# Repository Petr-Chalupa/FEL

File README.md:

<!-- omit from toc -->
# FEL
This repository contains selected coursework completed during my studies in
OI at CTU FEL. \
_If you found this repo. because you need help with some homework, do not copy, just get an inspiration :)_

<!-- omit from toc -->
## Theoretical Foundations
- LAG - Linear Algebra
- DMA - Discrete Mathematics
- LGR - Logic and Graph Theory
- MA1, MA2 - Mathematical Analysis I & II
- PST - Probability and Statistics
- NUM - Numerical Methods
- OPT - Optimization
- PKS - Computer and Communication Networks

<!-- omit from toc -->
## Programming & Engineering Courses
- [PRP - C](#prp---c)
- [RPH - Python](#rph---python)
- [PJV - Java](#pjv---java)
- [APO - Assembly \& C](#apo---assembly--c)
- [FUP - Racket \& Haskell](#fup---racket--haskell)
- [PSIA - C](#psia---c)
- [ALG - C](#alg---c)
- [OSY - Shell \& C](#osy---shell--c)
- [KEO - Hardware](#keo---hardware)
- [PDV - C++ \& Java](#pdv---c--java)
- [ZUI - Python](#zui---python)
- [DBS - SQL \& Java](#dbs---sql--java)

### PRP - C
- Command Line Tools ~ utilities demonstrating C programming concepts:
  - Array and string manipulation (hw01, hw02)
  - File operations and parsing (hw03)
  - Data structures implementation (hw04, hw05)
  - Memory management (hw06)
  - Custom grep implementation (hw07)
- Graph Algorithms ~ implementations of fundamental graph operations and algorithms:
  - Queue implemetation (hw08)
  - File I/O for both text and binary formats (hw09)
  - Memory management with dynamic allocation (hw09)
  - Implementations of various graph algorithms (hw10)
  - _Note: hw10 framework was provided, my contribution was integration of specific functions (pq_update, dijkstra_set_graph, dijkstra_get_solution, graph.c)_

### RPH - Python
- Spam Filter ~ a modular email classification system with various spam detection methods:
  - Multiple filter types (Naive, Paranoid, Random and advanced heuristic Filter)
  - Analyzes email headers, domains, subject keywords, text patterns and links
  - Uses confusion matrix for quality assessment
  - Training and testing on email corpus data
- Reversi ~ a player implementation for the Reversi board game:
  - Heuristic-based move selection
  - Position rating matrix
  - Valid move detection with weighted decision-making
  - Complete game rules implementation

### PJV - Java
- Core Java Concepts - Standalone assignments demonstrating Java fundamentals:
  - Calculator (console-based arithmetic operations)
  - CircularArrayQueue (queue implementation with fixed capacity)
  - SequenceStats (statistical calculations on number sequences)
  - BruteForceAttacker (recursive password cracking with a character set)
  - Tree & Node (binary tree with recursive traversal and string representation)
- [2D Game Engine](https://github.com/Petr-Chalupa/JTileEngine) - Semester project implementing a custom 2D game engine in JavaFX

### APO - Assembly & C
- Assembly Assignments (RISC-V):
  - Array manipulation and sorting algorithms in assembly (hw02.S, lab01.S, lab02.S)
  - Serial port I/O echo implementation (lab03.S)
  - Fibonacci sequence generation on a pipelined CPU (hw03.S)
  - 32-bit word to hexadecimal digits conversion and serial port output (hw04.S)
  - _Note: All assembly code is tested in [QtRVSim](https://github.com/cvut/qtrvsim) - a RISC-V simulator_
- C Assignments:
  - Image convolution using a mask (hw01.c)
  - UART calculator for adding unsigned numbers, built without static libraries (hw05.c)
    - _Note: hw05_crt0.S was provided as a minimal replacement for C runtime_
  - Simple LCD program (lab04.c)
- Pong Game (C):
  - Implementation of the classic Pong game for the MZ-APO educational board
  - Features:
    - Real-time graphics rendering on the LCD
    - Paddle and ball movement with collision detection
    - Score tracking and high scores
    - Modular code structure for hardware abstraction
  - _Note: Only the following files are my original work:_
    - _`pong.c`, `utils.c`, `IO_utils.c`, `logo.c` and their respective header files in `include/`_
    - _Other files (e.g., hardware abstraction, font data) were provided as part of the assignment framework._

### FUP - Racket & Haskell
- Racket Assignments:
  - Image Processing ~ ASCII art generation from images (hw01):
    - Image to grayscale matrix conversion
    - Matrix scaling and transformation
    - ASCII character mapping based on pixel intensity
    - Support for custom character sets and block sizes
  - SVG Generator ~ declarative SVG generation (hw02):
    - Dynamic SVG element creation
    - Support for basic shapes (circle, rect, line)
    - Expression evaluation with environments
    - Conditional rendering capabilities
  - Exam assigment - Manhattan distance (exam01.rkt):
    - Assigns symbols to grid cells based on proximity to given points
    - Handles ties and exact matches with special symbols
- Haskell Assignments:
  - λ-Calculus Evaluator (Hw03)
    - Lambda calculus interpreter with normal order reduction
    - Alpha conversion, beta reduction and capture-avoiding substitution
    - Leftmost redex finding for proper evaluation order
    - Expression representation for variables, applications, and abstractions
  - Parser of λ-programs (Hw04)
    - Parser implementation for λ-calculus expressions
    - Support for variable definitions and substitutions
    - _Note: Parser monad implementation was provided_
  - Exam assigment - Minimum spanning tree (Exam02.hs):
    - Minimum spanning tree computation using Jarník's algorithm
    - Custom graph and edge data types
    - Handles undirected graphs by edge reversal

### PSIA - C
- Network Programming ~ UDP File Transfer:
    - CRC32 packet verification
    - MD5 file integrity check
    - Selective repeat and stop-and-wait for flow control
    - Automatic retry on packet loss
    - Configurable window size and packet size
  - Client-Server Architecture
    - Configurable ports and IP addresses
  - File Operations
    - Binary file transfer support
    - Integrity verification
  - _Note: [md5](https://github.com/Zunawe/md5-c) is a publicly available library_

### ALG - C
- Duplicate Number Finder (hw00.c):
    - Training exercise
- Park Designer (hw01.c):
    - Optimizes park layout with specific constraints:
      - Central area must contain minimum number of rocks
      - Maximizes number of forest tiles in total area
    - Uses prefix sum arrays for efficient area calculations
- Agent Placement (hw02.c):
    - Optimizes agent placement in a graph:
      - Type A scores based on occupied neighbors
      - Type B scores based on unoccupied neighbors
    - Uses backtracking with pruning optimizations
- Tree Path Finder (hw03.c):
    - Finds longest valid path in a tri-colored tree:
      - Path cannot contain 3 consecutive same-colored nodes
    - Uses recursive DFS with path validation
    - Queue-based tree construction from level-order input
- Mouse vs Cat Path (hw04.c):
    - Finds shortest "safe" path for a mouse while avoiding the cat:
      - Graph nodes can be "noisy"; visiting noisy nodes alerts the cat
      - Mouse must avoid positions reachable by the cat within constrained jumps
    - Uses multi-state per node storage and BFS with pruning to return (distance, noisy_used) for optimal path
- Binary search tree with lazy deletion (hw05.c):
    - Implements a BST that supports `ins K` and `del K` commands.
    - Uses lazy deletion and periodically compacts the tree when the sum of deleted-node heights exceeds the sum of active-node heights.
    - Compaction preserves pre-order of active nodes
- Turing machine simulator (hw06.c):
  - Decodes a compact machine encoding into transitions and simulates the machine
  - Checks whether the machine is deterministic and explores branching configurations using BFS
- Irrigatio (hw07.c):
  - Selects high-value horizontal/vertical segments using prefix-sums
  - Sorts segments by weight and combines them via DP for optimal total value
- Totem Buyer (hw08.c):
  - Maximizes profit from buying totems between villages and selling them
  - Villages merge when their separating totem is purchased
  - Purchase cost depends on warrior count difference between villages
  - Similar structure to matrix chain multiplication problem
- Triples (exam.c):
  - Finds non-overlapping 3-cell segments (horizontal and vertical) in a colored matrix
  - Scores each segment: 3 points for all same color, 1 point for 2 same colors, 0 points otherwise
  - Uses backtracking to maximize total score by selecting optimal segment combinations
  - Includes pruning optimization with greedy upper bound calculation for performance

### OSY - Shell & C
- Shell Scripting:
  - File System Path Processor (hw01.sh):
    - Processes paths from stdin (prefixed with "PATH ")
    - Optional .tgz archive creation (-z flag)
  - Text Processing Utilities (hw02.sh):
    - PDF file listing with case-insensitive sorting
    - Number-prefixed line filtering
    - Sentence extraction and formatting
    - C #include directive prefix manipulation
- Unix Programming:
  - Process forking and piping (hw03):
    - Parent-child process communication via pipes
    - Random number generator with signal handling
    - Integration with provided GCD calculator
    - _Note: `nsd_src` (GCD calculator) was provided as part of the assignment_
  - Producer-Consumer Threading (hw04):
    - Multithreaded word processing with shared list
    - Mutex-protected stdout and list operations
    - Conditional variables for synchronization
  - Factory Simulation (hw05):
    - Command-driven factory simulator reading commands from stdin
    - Worker threads process product steps at named places
    - Synchronization with mutexes and condition variables
    - Dynamic worker management and resource accounting
  - Hexadecimal Converter (hw06):
    - Reads unsigned integers from stdin and prints them as hexadecimal
    - Implementation using direct syscalls
    - Built with no libc
- Nova Microkernel Assignments:
  - nbrk system call (ec_syscall.cc):
    - Handles dynamic memory with page table operations and allocation/deallocation
  - User-space memory allocator (mem_alloc.c):
    - Custom heap management for user programs
    - Integrates with kernel page management
  - Thread management system calls (ec_syscall.cc):
    - thread_create: Creates new threads with user-provided stack
    - thread_yield: Switches execution context to the next thread in buffer
    - Circular queue scheduler
  - _Note: Nova kernel framework, build system, and infrastructure were provided; my contributions are `ec_syscall.cc` and `mem_alloc.c`._
    - _The kernel framework provides: CPU/MMU abstraction (`cpu.h`, `ptab.h`), physical memory manager (`kalloc.h`), execution context infrastructure (`ec.h`)..._

### KEO - Hardware
- Complete PCB project design and realization
- Documentation: [`Prezentace.pdf`](KEO/Prezentace.pdf), [`Protokol.pdf`](KEO/Protokol.pdf), [`Schema.pdf`](KEO/Schema.pdf), [`DPS.pdf`](KEO/DPS.pdf)
- Design files: [`Zdroj.kicad_sch`](KEO/Zdroj/Zdroj.kicad_sch), [`Zdroj.kicad_pcb`](KEO/Zdroj/Zdroj.kicad_pcb), [`Zdroj.kicad_pro`](KEO/Zdroj/Zdroj.kicad_pro)

### PDV - C++ & Java
- Parallel (C++):
  - Producer-Consumer Threading (hw01):
    - Generic thread pool template with parametrized job and worker types
    - Producer-consumer coordination without busy-waiting
  - Vector Sum (hw02):
    - Parallel array summation using various OpenMP scheduling strategies
    - Comparison of `static` vs. `dynamic` scheduling performance for uneven workloads
    - Analysis of load balancing trade-offs
  - Lock-Free BST (hw03):
    - Thread-safe binary search tree using atomic operations and lock-free synchronization
    - Lock-free insertion and deletion with compare-and-swap operations
  - Parallel Database Query (hw04):
    - Evaluation of universal and existential predicates
    - Early termination using #pragma omp cancel for
  - Parallel Radix Sort (hw05):
    - Recursive MSD radix sort implementation for strings
    - Parallelized using recursive sub-sorting of buckets
- Distributed (Java):
  - BFS and IDDFS (hw06):
    - Parallel implementations of breadth-first search and iterative deepening depth-first search
    - _Note: Framework files were provided as part of the assignment_
  - SWIM Protocol (hw07):
    - Implementation of the SWIM failure detection protocol with custom active strategy and ping message handling
    - _Note: Framework files were provided as part of the assignment_
  - Ricart-Agrawala Mutual Exclusion (hw08):
    - Implementation of the Ricart-Agrawala algorithm for distributed mutual exclusion with logical clocks and message passing for critical sections coordination
    - _Note: Framework files were provided as part of the assignment_
  - RAFT Consensus (hw09):
    - Implementation of the RAFT distributed consensus protocol for replicated state machines
    - Leader election, log replication, and follower heartbeats with safety under message loss
    - Message classes for vote requests/responses and append entries for cluster coordination
    - _Note: Framework files were provided as part of the assignment_

### ZUI - Python
- Blocks World Solver (hw01):
  - A* search algorithm with custom heuristic for solving the blocks world puzzle
  - Heuristic based on correct prefix matching of goal stacks
  - Finds optimal sequence of block moves to reach goal configuration
  - _Note: blockworld.py environment was provided as part of the assignment_
- Tabular Q-Learning (hw02):
  - Reinforcement learning agent using tabular Q-learning to solve the blocks world puzzle
  - Custom implementation for training and evaluation
  - _Note: blockworld.py environment was provided as part of the assignment_
- OX Game Solver (hw03):
  - Implements Tic-Tac-Toe/OX game logic with self-play and move evaluation
  - Uses Monte Carlo Tree Search guided by a neural network model for position assessment
  - _Note: ox.py environment was provided as part of the assignment_

### DBS - SQL & Java
- Database Systems ~ SQL & Java assignments demonstrating relational modeling, ER design, and query construction
- Practical SQL problem solving and database design
  - _Note: `CP5.java` is the main important class in this section of assignment_

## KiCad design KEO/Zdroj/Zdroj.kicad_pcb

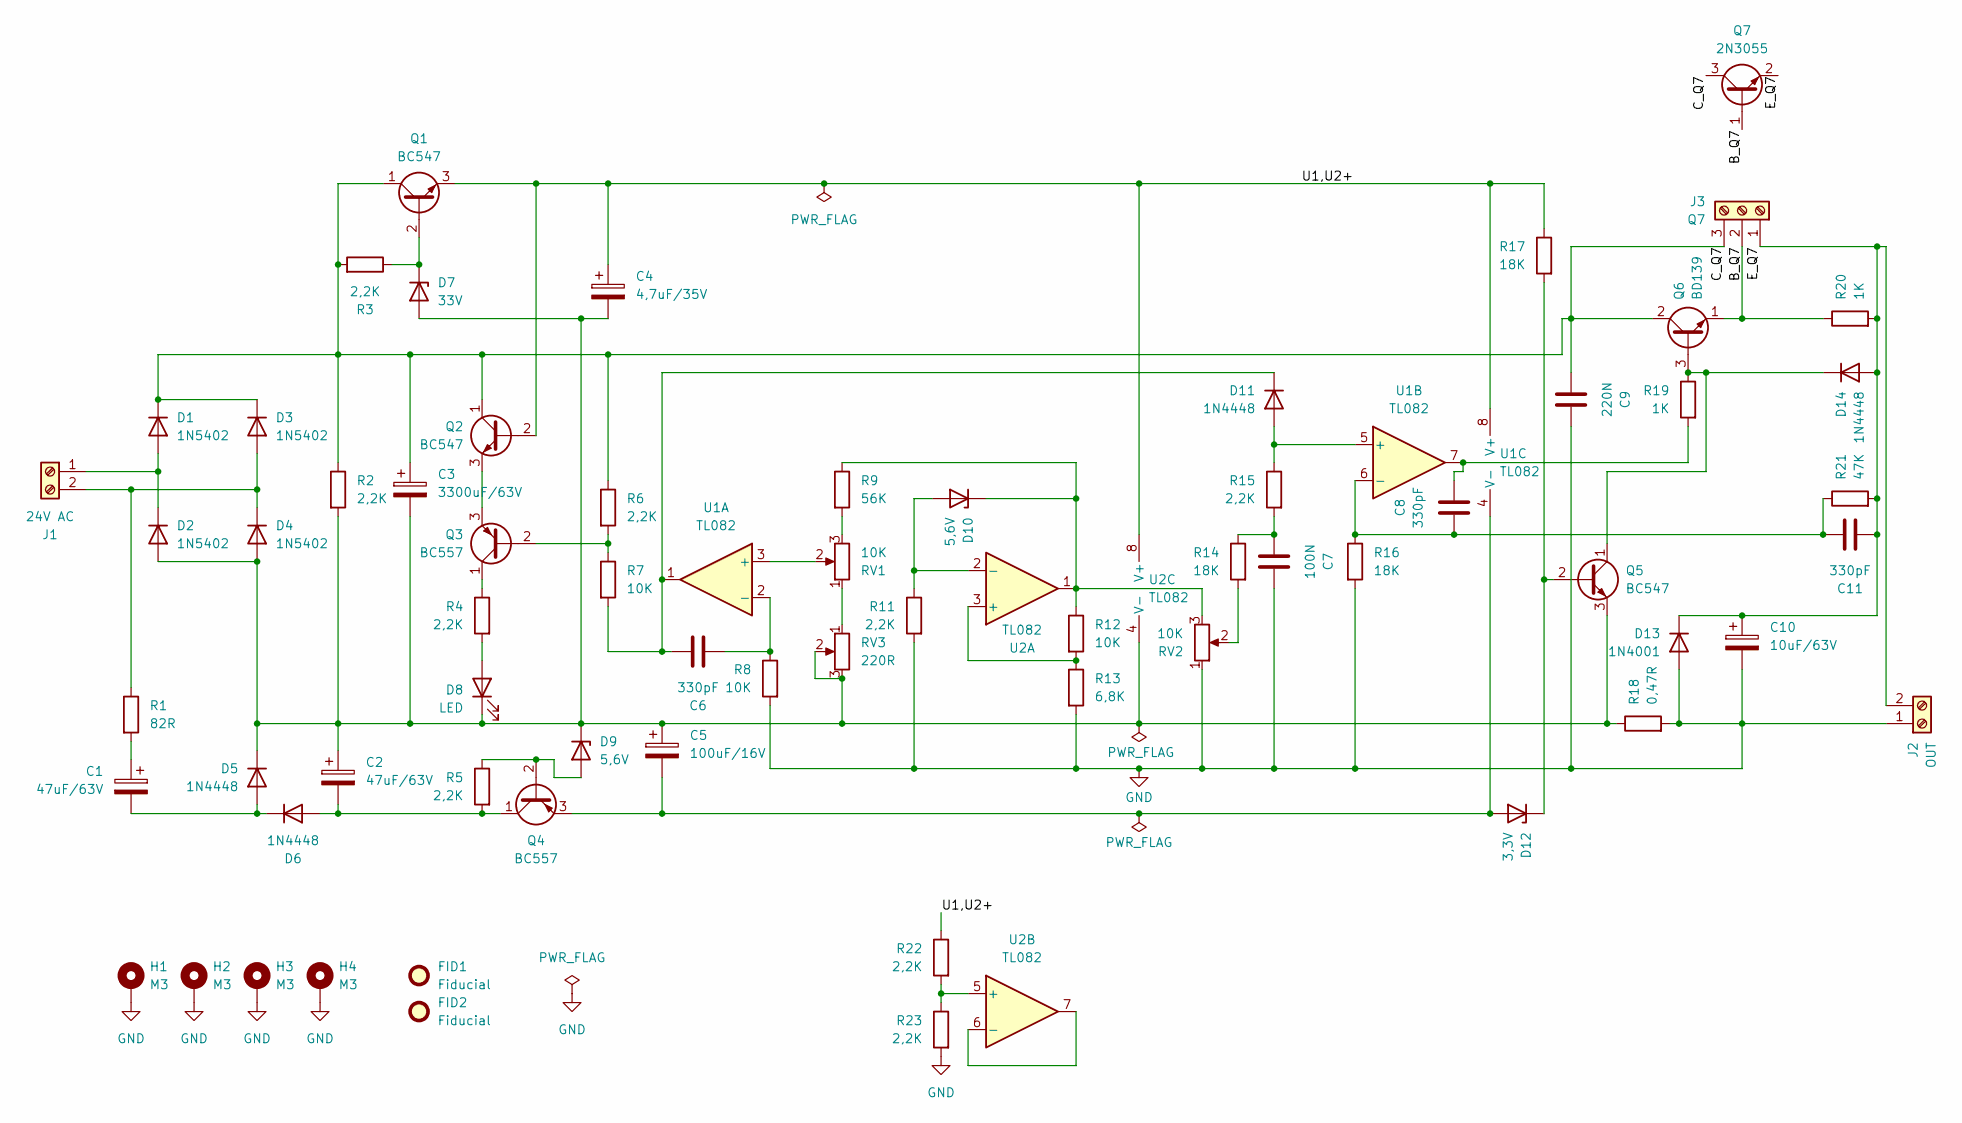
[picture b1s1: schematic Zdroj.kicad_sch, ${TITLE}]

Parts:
C1, C2: 47uF/63V; CP_Radial_D10.0mm_P5.00mm
C3: 3300uF/63V; CP_Radial_D22.0mm_P10.00mm_SnapIn
C4: 4,7uF/35V; CP_Radial_D5.0mm_P2.00mm
C5: 100uF/16V; CP_Radial_D6.3mm_P2.50mm
C6, C8, C11: 330pF; C_Disc_D5.0mm_W2.5mm_P5.00mm
C7: 100N; C_Rect_L7.0mm_W2.5mm_P5.00mm
C9: 220N; C_Rect_L7.0mm_W2.5mm_P5.00mm
C10: 10uF/63V; CP_Radial_D6.3mm_P2.50mm
D1, D2, D3, D4: 1N5402; D_DO-201AD_P15.24mm_Horizontal
D5, D6, D11, D14: 1N4448; D_DO-35_SOD27_P7.62mm_Horizontal
D7: 33V; D_DO-35_SOD27_P7.62mm_Horizontal
D8: LED; LED_D5.0mm
D9, D10: 5,6V; D_DO-35_SOD27_P7.62mm_Horizontal
D12: 3,3V; D_DO-35_SOD27_P7.62mm_Horizontal
D13: 1N4001; D_DO-41_SOD81_P10.16mm_Horizontal
FID1, FID2: Fiducial; Fiducial_0.5mm_Mask1mm
H1, H2, H3, H4: M3; MountingHole_3.2mm_M3_DIN965_Pad
J1: 24V AC; TerminalBlock_Phoenix_MKDS-3-2-5.08_1x02_P5.08mm_Horizontal
J2: OUT; TerminalBlock_Phoenix_MKDS-3-2-5.08_1x02_P5.08mm_Horizontal
J3: Q7; TerminalBlock_Phoenix_MKDS-1,5-3-5.08_1x03_P5.08mm_Horizont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
Q1, Q2, Q5: BC547; TO-92_Inline
Q3, Q4: BC557; TO-92_Inline
Q6: BD139; TO-126-3_Vertical
Q7: 2N3055; TO-3
R1: 82R; R_Axial_DIN0207_L6.3mm_D2.5mm_P7.62mm_Horizontal
R2: 2,2K; R_Axial_DIN0414_L11.9mm_D4.5mm_P15.24mm_Horizontal
R3, R4, R5, R6, R11, R15, R22, R23: 2,2K; R_Axial_DIN0207_L6.3mm_D2.5mm_P7.62mm_Horizontal
R7, R8, R12: 10K; R_Axial_DIN0207_L6.3mm_D2.5mm_P7.62mm_Horizontal
R9: 56K; R_Axial_DIN0207_L6.3mm_D2.5mm_P7.62mm_Horizontal
R13: 6,8K; R_Axial_DIN0207_L6.3mm_D2.5mm_P7.62mm_Horizontal
R14, R16, R17: 18K; R_Axial_DIN0207_L6.3mm_D2.5mm_P7.62mm_Horizontal
R18: 0,47R; R_Axial_Power_L25.0mm_W6.4mm_P30.48mm
R19, R20: 1K; R_Axial_DIN0207_L6.3mm_D2.5mm_P7.62mm_Horizontal
R21: 47K; R_Axial_DIN0207_L6.3mm_D2.5mm_P7.62mm_Horizontal
RV1, RV2: 10K; Potentiometer_Piher_PC-16_Single_Horizontal
RV3: 220R; Potentiometer_Piher_PT-6-V_Vertical
U1, U2: TL082; DIP-8_W7.62mm

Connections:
/B_Q7: J3.2, Q6.1 (E), Q7.1 (B), R20.1
/C_Q7: C3.1, C9.2, D1.1 (K), D3.1 (K), J3.3, Q1.1 (C), Q2.1 (C), Q6.2 (C), Q7.3 (C), R2.1, R3.2, R6.1
/E_Q7: C10.1, C11.1, D13.1 (K), D14.2 (A), J2.2, J3.1, Q7.2 (E), R20.2, R21.2
/U1,U2+: C4.1, Q1.3 (E), Q2.2 (B), R17.1, R22.1, U1.8 (V+), U2.8 (V+)
GND: C7.2, C9.1, C10.2, D13.2 (A), H1.1, H2.1, H3.1, H4.1, J2.1, R8.2, R11.2, R13.2, R16.2, R18.2, R23.2, RV2.1
unnamed: C1.1, R1.2
unnamed: C7.1, R14.1, R15.2
unnamed: C8.2, R19.2, U1.7
unnamed: D1.2 (A), D2.1 (K), J1.1
unnamed: C2.1, C3.2, C4.2, C5.1, D2.2 (A), D4.2 (A), D5.1 (K), D7.2 (A), D8.1 (K), D9.1 (K), Q5.3 (E), R2.2, R18.1, RV3.2, RV3.3, U2.4 (V-)
unnamed: D3.2 (A), D4.1 (K), J1.2, R1.1
unnamed: C1.2, D5.2 (A), D6.1 (K)
unnamed: C2.2, D6.2 (A), Q4.1 (C), R5.2
unnamed: D7.1 (K), Q1.2 (B), R3.1
unnamed: D8.2 (A), R4.2
unnamed: D9.2 (A), Q4.2 (B), R5.1
unnamed: D10.2 (A), R11.1, U2.2 (-)
unnamed: D10.1 (K), R9.1, R12.1, RV2.3, U2.1
unnamed: D11.2 (A), R15.1, U1.5 (+)
unnamed: C6.2, D11.1 (K), R7.2, U1.1
unnamed: C5.2, D12.2 (A), Q4.3 (E), U1.4 (V-)
unnamed: D12.1 (K), Q5.2 (B), R17.2
unnamed: D14.1 (K), Q5.1 (C), Q6.3 (B), R19.1
unnamed: Q2.3 (E), Q3.3 (E)
unnamed: Q3.2 (B), R6.2, R7.1
unnamed: Q3.1 (C), R4.1
unnamed: R9.2, RV1.3
unnamed: R14.2, RV2.2
unnamed: RV1.1, RV3.1
unnamed: RV1.2, U1.3 (+)
unnamed: C6.1, R8.1, U1.2 (-)
unnamed: C8.1, C11.2, R16.1, R21.1, U1.6 (-)
unnamed: R12.2, R13.1, U2.3 (+)
unnamed: R22.2, R23.1, U2.5 (+)
unnamed: U2.6 (-), U2.7

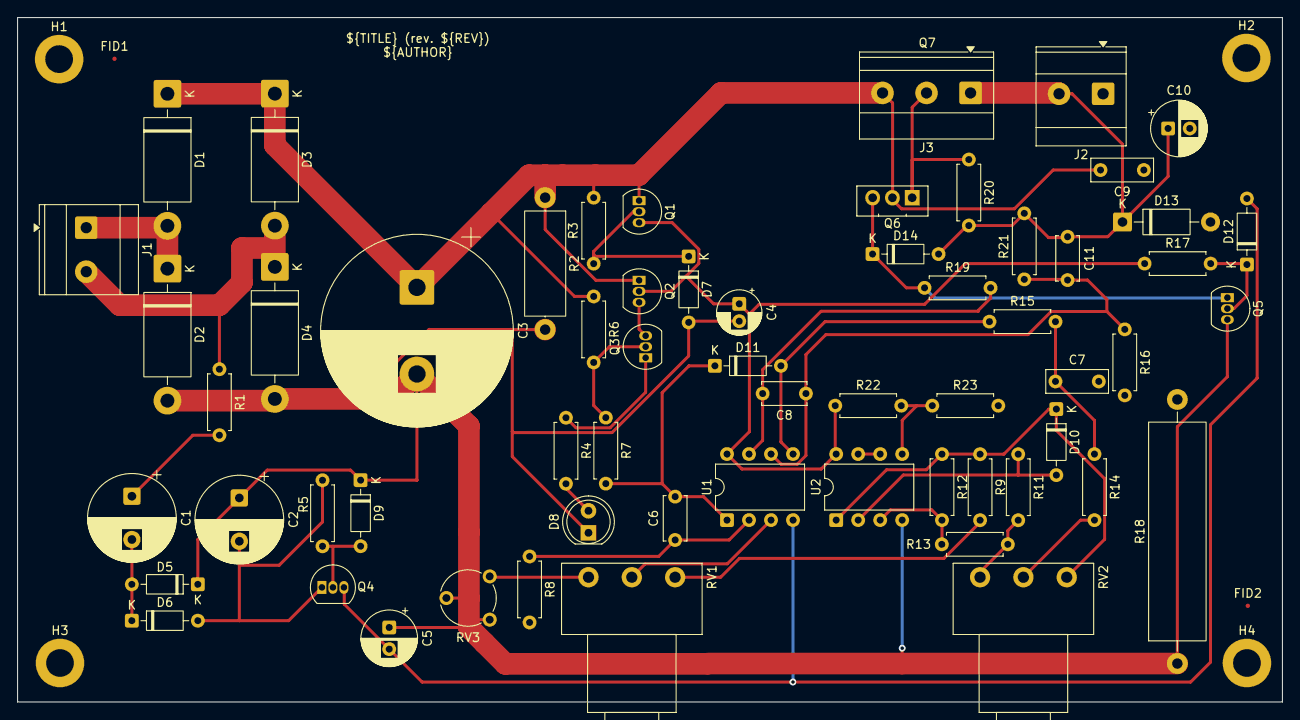
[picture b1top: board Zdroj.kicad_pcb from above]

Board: 2 copper layers, 146.0 x 79.0 mm, 67 parts (0 on the bottom side), 35 nets.

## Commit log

2025-04-09 Initial README, RPH
2025-04-10 RPH, PRP, PJV
2025-04-10 PJV bfa update
2025-04-10 FUP first two hws
2025-04-10 license update
2025-04-13 APO lab03 code
2025-04-13 Desc fix
2025-04-23 FUP hw3
2025-04-23 APO hw4b
2025-04-24 FUP fix
2025-05-01 APO hw05
2025-05-01 Apo hw5 overflow fix
2025-05-04 PJV engine link
2025-05-05 PSIA
2025-05-06 PSIA update
2025-05-07 Timeout fix, md5 incrementally
2025-05-12 FUP hw4
2025-05-28 APO Pong
2025-05-28 -RPH typst
2025-05-28 FUP exam
2025-05-28 Name fix
2025-10-03 ALG hw01
2025-10-06 ALG, OSY, KEO
2025-10-07 OSY hw02
2025-10-10 ALG hw02
2025-10-14 OSY hw03
2025-10-28 OSY hw04 & ALG hw03 & KEO project init
2025-11-11 OSY hw05
2025-11-12 OSY hw06
2025-11-16 ALG hw04
2025-11-16 Pouzdra
2025-11-16 Zdroj power net class
2025-11-17 Téměř celá DPS
2025-11-17 Author text on PCB
2025-11-18 KEO GND
2025-11-18 KEO Drobné úpravy
2025-11-21 ALG hw05
2025-11-24 ALG hw06
2025-12-30 KEO protokol; Alg 7, 8; Osy nova
2026-01-08 Readme fixes
2026-03-16 PDV hw01, 02, 03
2026-03-20 ZUI hw01
2026-04-08 PDV hw04 & hw05
2026-05-08 PDV hw06
2026-05-08 PDV hw06 & 07, ZUI hw02
2026-05-11 PDV hw08
2026-05-15 ZUI hw03, PDV hw09
